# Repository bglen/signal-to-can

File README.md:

# signal-to-can device

Measures analog and digital signals and converts readings to CAN bus messages. Easilly powered by 12V automotive systems to make CAN bus datalogging in your vehicle easy.

- 8 ADC inputs with seperate signal grounds
  
- CAN 2.0b communication output
  
- Fully configurable through the CAN interface
  
- 3.3V and 5V sensor power supply
  
- Easilly powered by 12V automotive systems

- Per-channel configurable voltage offset and scaling

- Per-channel configurable out-of-range limits

- Pre-made DBC file you can use or edit as a template

### Enclosure

The repo contains a 3D-printable enclosure. We reccomend ASA, ABS, PC-ABS, or Nylon for automotive enviornments.

Front            |  Rear
:-------------------------:|:-------------------------:
  |  

### TODO
- Update board with schematic changes
- Calibration test points
- Choose new potentiometer for rev 2
- configuration CAN message

# CAN Messages

All messages are big-endian (Motorola).

## Output Messages

| Name             | ID            | DLC     | Bytes 0-1 | Bytes 2-3 | Bytes 4-5 | Bytes 6-7 |
| -----------      | -----------   | ------- | --------- | --------- | --------- | --------- |
| ADC Values 0 - 3 | node_id + 0x1 | 8 bytes | adc_0     | adc_1     | adc_2     | adc_3     |
| ADC Values 4 - 7 | node_id + 0x2 | 8 bytes | adc_4     | adc_5     | adc_6     | adc_7     |

| Name          | ID            | DLC     | Bytes 0-1  | Bytes 2-3 | Bytes 4-5 | Bytes 6-7  |
| -----------   | -----------   | ------- | ---------- | --------- | --------- | ---------- |
| Device Status | node_id + 0x3 | 8 bytes | adc_status | uptime    | v_supply  | fw_version |

### Parameters

**adc_0 to adc_7:** uint16, ontains the output value for each analog channel.

**adc_status:** uint16, Bit structure containing the current status for each channel. Each channel gets two bits starting with channel 0 to channel 7.

| 2-bit value  | Status            |
| -----------  | ----------------- |
| 00           | Inactive          |
| 01           | Active            |
| 10           | Out-of-range low  |
| 11           | Out-of-range high |

Example: adc_satus = 00011001010111 -> channel 0 inactive, channel 1 active, channel 3 out-of-range low, channel 4 active, channel 5 active, channel 6 active, channel 7 out-of-range high.

**uptime:** uint16, Seconds since power-on, wraps at 65535.

**v_supply:** uint16, Device supply voltage in mV.

**fw_version** uint16, Device firmware version.

## Command Message

A single CAN ID is used for all command messages. The device will respond with an acknoledge message after receiving the command message.

| Name            | ID            | DLC     | Byte 0  | Byte 1 | Byte 2 | Byte 3 | Byte 4 | Byte 5 | Byte 6 | Byte 7 |
| -----------     | ------------- | ------- | ------- | -----  | -----  | -----  | -----  | -----  | -----  | -----  |
| Command Message | node_id + 0x5 | 8 bytes | com     | d1     | d2     | d3     | d4     | d5     | d6     | d7     |
| Ack Message     | node_id + 0x6 | 1 bytes | success |        |        |        |        |        |        |        |

### Command Codes

| Command Name       | Command Code (com) | d1             | d2             | d3              | d4              | d5         | d6        | d7 |
| ------------------ | ------------------ | -------------- | -------------- | --------------- | --------------- | ---------- | --------- | -- |
| SET_BAUD           | 1                  | baud_enum      | 0              | 0               | 0               | 0          | 0         | 0  |
| SET_SAMPLE_RATE    | 2                  | sample_rate[0] | sample_rate[1] | 0               | 0               | 0          | 0         | 0  |
| SET_CHANNEL        | 3                  | channel        | enable_bit     | scale_factor[0] | scale_factor[1] | offset[0]  | offset[1] | 0  |
| SET_CHANNEL_RANGE  | 4                  | channel        | oor_min[0]     | oor_min[1]      | oor_max[0]      | oor_max[1] | 0         | 0  |
| GET_VALUE          | 5                  | channel        | selection      | 0               | 0               | 0          | 0         | 0  |

### Parameters

**com:** uint8, Command code. Use the table below to specify a particular command and structure the data

**d1 to d5 :** unint8, Command-specific data.

**success:** uint8, 1 if command executed successfully, 0 if there was an error.

**baud_enum:** uint8, Enum representing the desired baud rate.

| baud_enum | Baud Rate |
| --------- | --------- |
| 0         | 125 kbps  |
| 1         | 250 kbps  |
| 2         | 500 kbps  |
| 3         | 1 Mbps    |

**sample_rate:** uint16, Sample rate of the device in Hz. All channels are sampled at the same rate.

**channel:** uint8, Channel number from 0 to 7.

**enable_bit:** uint8, 0 -> inactive, 1 -> active.

**scale_factor:** uint16, Scale factor to convert the channel voltage to a useful value.

**offset:** uint16, Channel offset value, used with scale factor to convert the channel voltage to a useful value.

**oor_min:** uint16, Out of range minimum value. Used to detect issues with the channel, wiring, or sensor. Specify as a voltage in milivolts, from 0 to 3300. Must be less than the oor_max for that channel.

**oor_max:** uint16, Out of range maximum value. Used to detect issues with the channel, wiring, or sensor. Specify as a voltage in milivolts, from 0 to 3300.

**selection:** uint8, Enum representing the desired value to be returned.

| selection | Value to be returned |
| --------- | -------------------- |
| 0         | sample_rate          |
| 1         | scale_factor         |
| 2         | offset               |
| 3         | oor_min              |
| 4         | oor_max              |

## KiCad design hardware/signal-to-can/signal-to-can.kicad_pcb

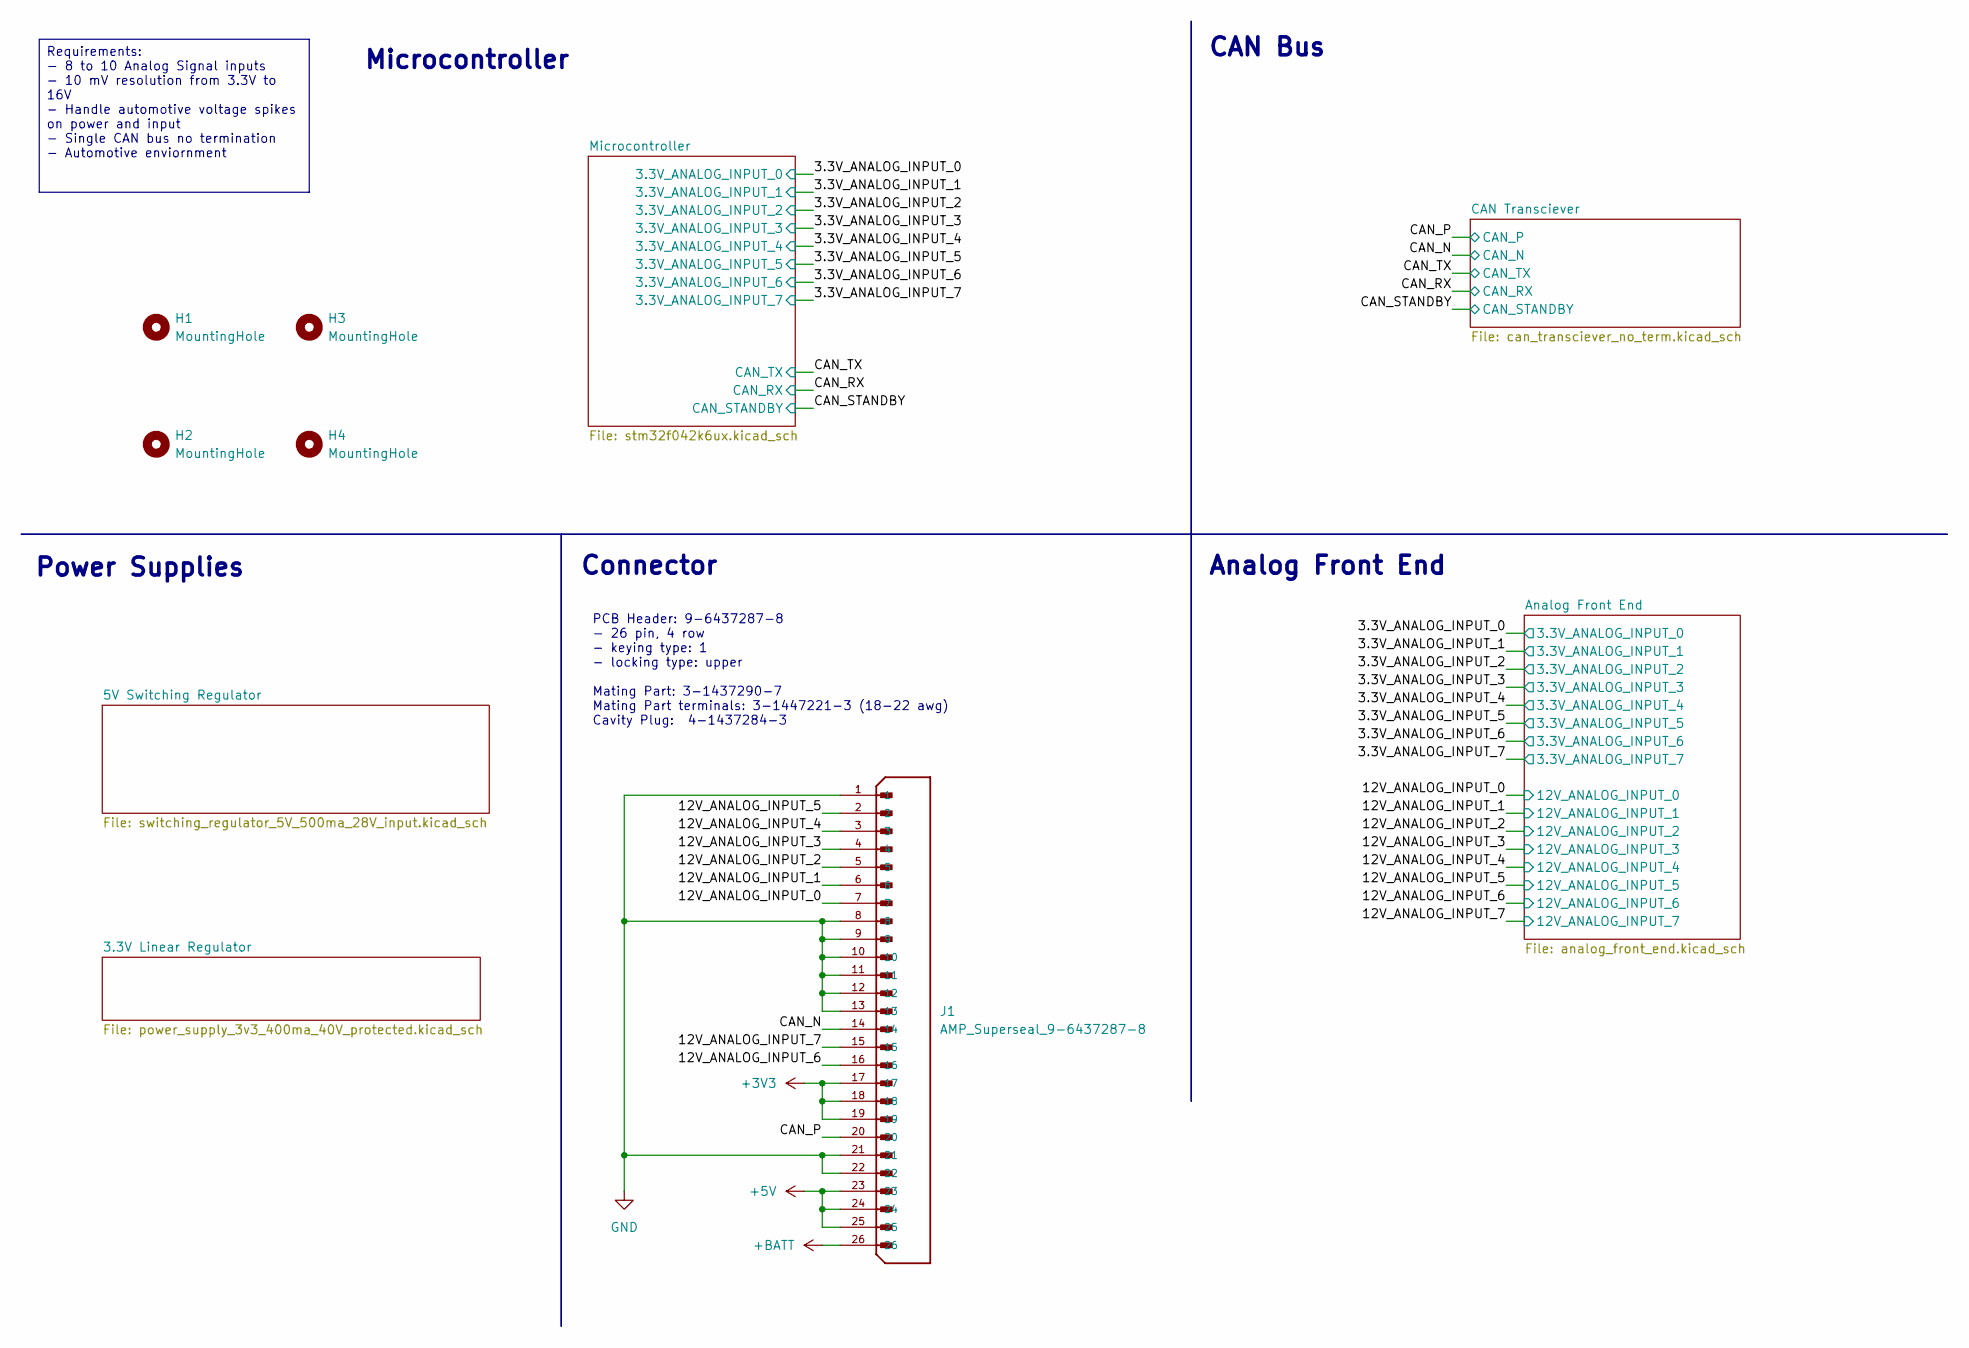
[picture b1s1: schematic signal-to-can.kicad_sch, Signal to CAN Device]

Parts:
H1, H2, H3, H4: MountingHole; MountingHole_3.2mm_M3
J1: AMP_Superseal_9-6437287-8; TE_9-6437287-8_1; PARTREV A1

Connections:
+3V3: J1.17, J1.18, J1.19; also elsewhere on the board
+5V: J1.23, J1.24, J1.25; also elsewhere on the board
+BATT: J1.26; also elsewhere on the board
/12V_ANALOG_INPUT_0: J1.7; also elsewhere on the board
/12V_ANALOG_INPUT_1: J1.6; also elsewhere on the board
/12V_ANALOG_INPUT_2: J1.5; also elsewhere on the board
/12V_ANALOG_INPUT_3: J1.4; also elsewhere on the board
/12V_ANALOG_INPUT_4: J1.3; also elsewhere on the board
/12V_ANALOG_INPUT_5: J1.2; also elsewhere on the board
/12V_ANALOG_INPUT_6: J1.16; also elsewhere on the board
/12V_ANALOG_INPUT_7: J1.15; also elsewhere on the board
/CAN_N: J1.14; also elsewhere on the board
/CAN_P: J1.20; also elsewhere on the board
GND: J1.1, J1.8, J1.9, J1.10, J1.11, J1.12, J1.13, J1.21, J1.22; also elsewhere on the board

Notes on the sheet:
Connector
Analog Front End
PCB Header: 9-6437287-8 - 26 pin, 4 row - keying type: 1 - locking type: upper Mating Part: 3-1437290-7 Mating Part terminals: 3-1447221-3 (18-22 awg) Cavity Plug: 4-1437284-3
Power Supplies
CAN Bus
Microcontroller
Requirements: - 8 to 10 Analog Signal inputs - 10 mV resolution from 3.3V to 16V - Handle automotive voltage spikes on power and input - Single CAN bus no termination - Automotive enviornment

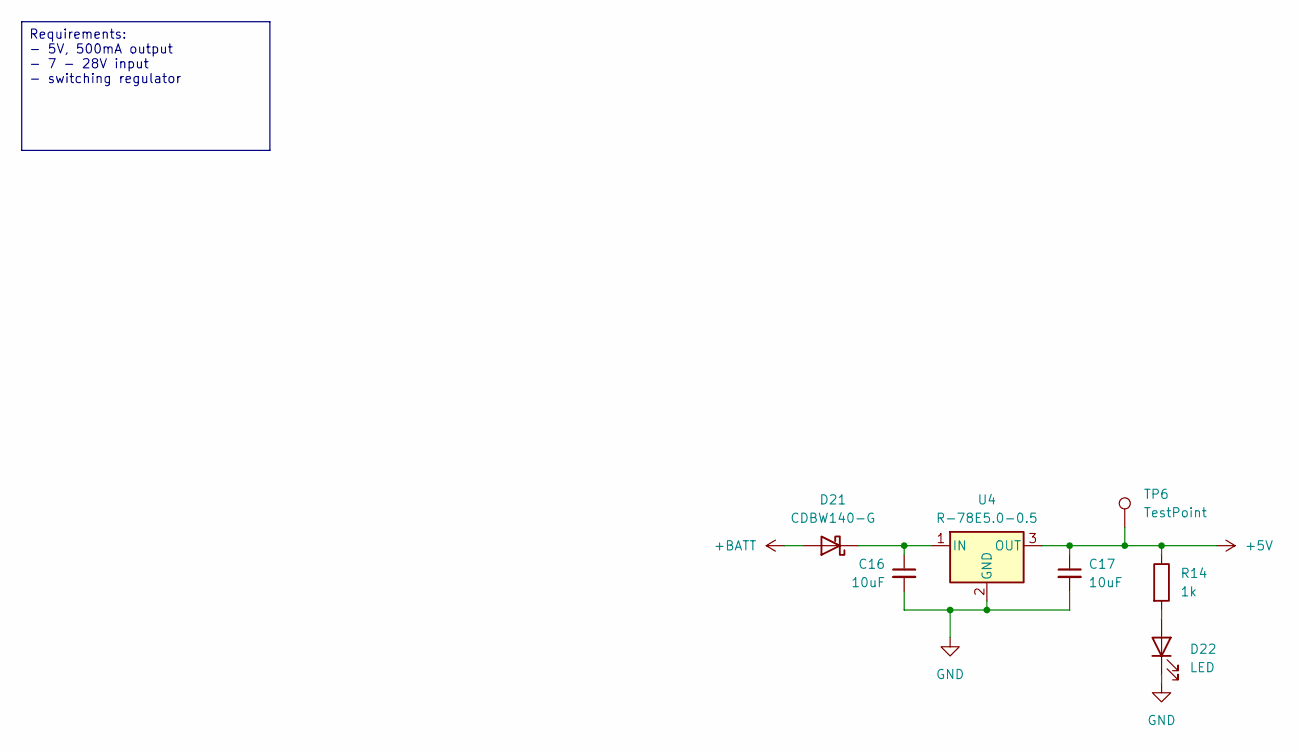
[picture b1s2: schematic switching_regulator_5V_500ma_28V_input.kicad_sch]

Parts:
C16, C17: 10uF; C_0603_1608Metric
D21: CDBW140-G; D_SOD-123
D22: LED; LED_0603_1608Metric
R14: 1k; R_0603_1608Metric
TP6: TestPoint; TestPoint_Pad_D1.0mm
U4: R-78E5.0-0.5; Converter_DCDC_RECOM_R-78E-0.5_THT

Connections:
+5V: C17.1, R14.1, TP6.1, U4.3 (OUT); also elsewhere on the board
+BATT: D21.2 (A); also elsewhere on the board
GND: C16.2, C17.2, D22.1 (K), U4.2 (GND); also elsewhere on the board
unnamed: C16.1, D21.1 (K), U4.1 (IN)
unnamed: D22.2 (A), R14.2

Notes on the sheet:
Requirements: - 5V, 500mA output - 7 - 28V input - switching regulator

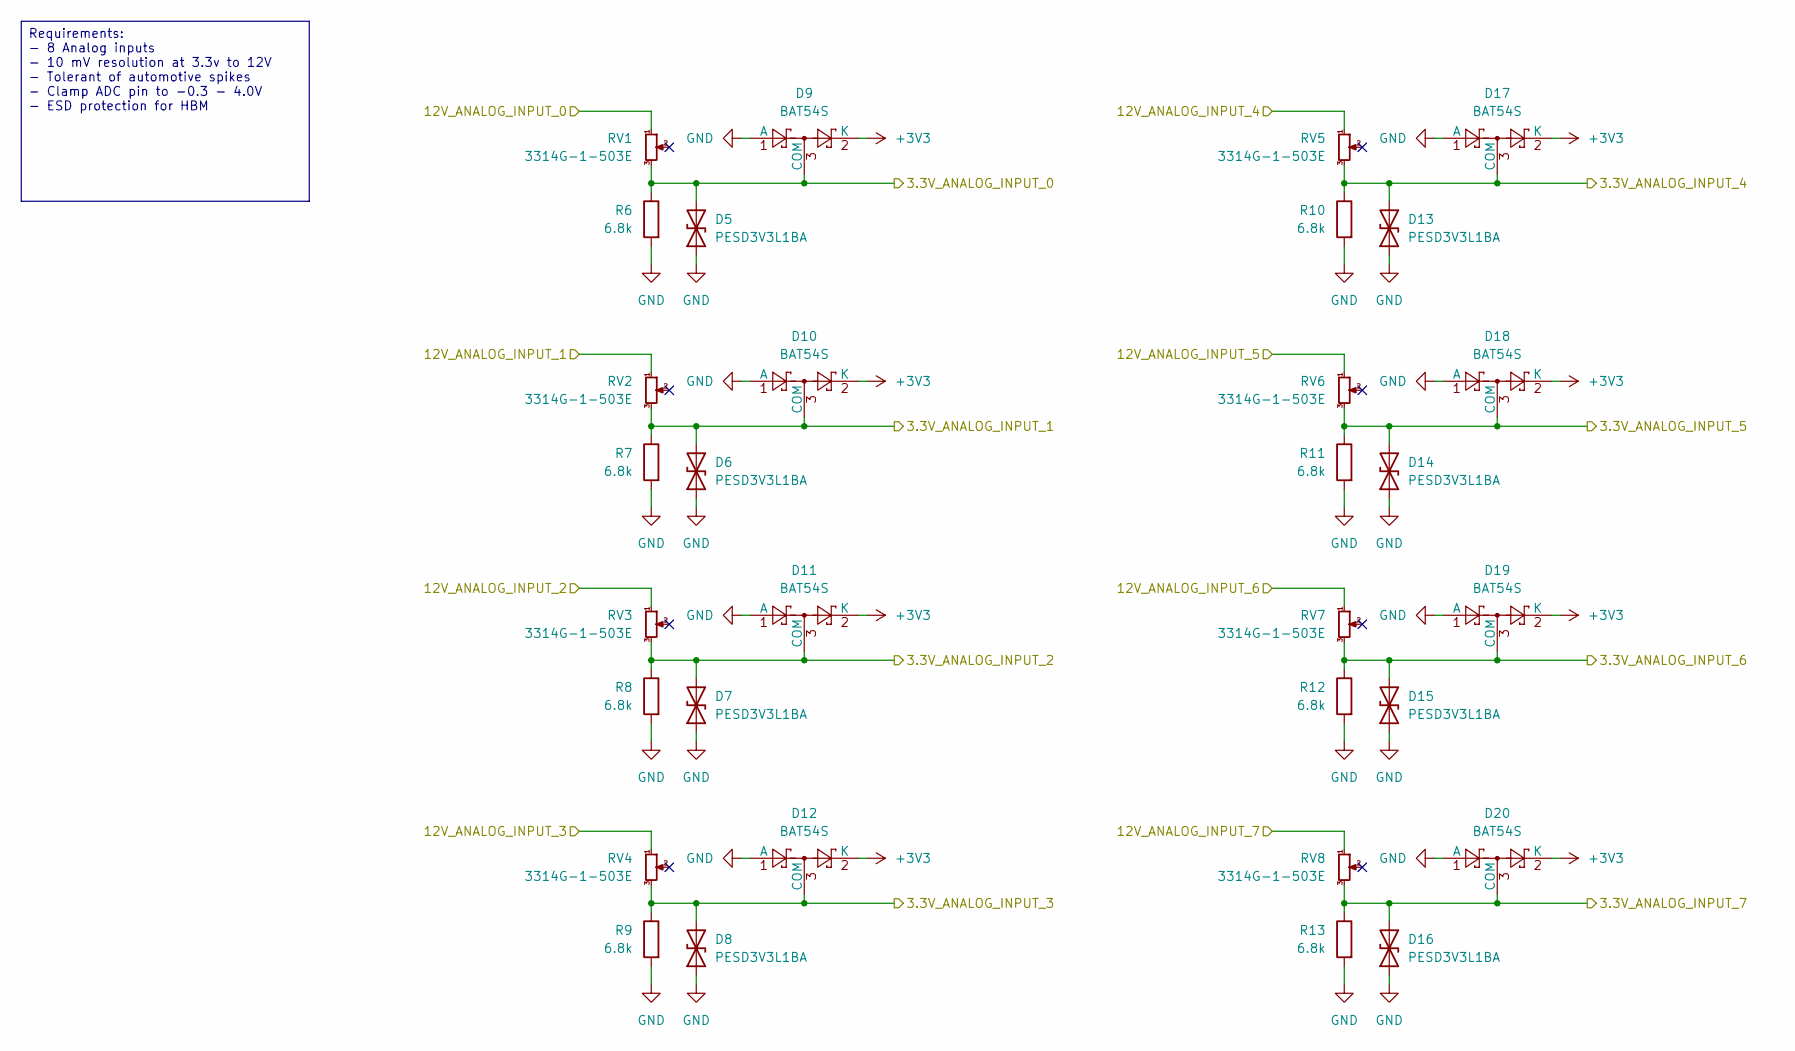
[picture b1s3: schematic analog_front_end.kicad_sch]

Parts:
D5, D6, D7, D8, D13, D14, D15, D16: PESD3V3L1BA; D_SOD-323
D9, D10, D11, D12, D17, D18, D19, D20: BAT54S; SOT-23
R6, R7, R8, R9, R10, R11, R12, R13: 6.8k; R_0603_1608Metric
RV1, RV2, RV3, RV4, RV5, RV6, RV7, RV8: 3314G-1-503E; Potentiometer_Bourns_3314G_Vertical

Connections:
+3V3: D9.2 (K), D10.2 (K), D11.2 (K), D12.2 (K), D17.2 (K), D18.2 (K), D19.2 (K), D20.2 (K); also elsewhere on the board
/3.3V_ANALOG_INPUT_0: D5.2 (A2), D9.3 (COM), R6.1, RV1.3; also elsewhere on the board
/3.3V_ANALOG_INPUT_1: D6.2 (A2), D10.3 (COM), R7.1, RV2.3; also elsewhere on the board
/3.3V_ANALOG_INPUT_2: D7.2 (A2), D11.3 (COM), R8.1, RV3.3; also elsewhere on the board
/3.3V_ANALOG_INPUT_3: D8.2 (A2), D12.3 (COM), R9.1, RV4.3; also elsewhere on the board
/3.3V_ANALOG_INPUT_4: D13.2 (A2), D17.3 (COM), R10.1, RV5.3; also elsewhere on the board
/3.3V_ANALOG_INPUT_5: D14.2 (A2), D18.3 (COM), R11.1, RV6.3; also elsewhere on the board
/3.3V_ANALOG_INPUT_6: D15.2 (A2), D19.3 (COM), R12.1, RV7.3; also elsewhere on the board
/3.3V_ANALOG_INPUT_7: D16.2 (A2), D20.3 (COM), R13.1, RV8.3; also elsewhere on the board
/12V_ANALOG_INPUT_0: RV1.1; also elsewhere on the board
/12V_ANALOG_INPUT_1: RV2.1; also elsewhere on the board
/12V_ANALOG_INPUT_2: RV3.1; also elsewhere on the board
/12V_ANALOG_INPUT_3: RV4.1; also elsewhere on the board
/12V_ANALOG_INPUT_4: RV5.1; also elsewhere on the board
/12V_ANALOG_INPUT_5: RV6.1; also elsewhere on the board
/12V_ANALOG_INPUT_6: RV7.1; also elsewhere on the board
/12V_ANALOG_INPUT_7: RV8.1; also elsewhere on the board
GND: D5.1 (A1), D6.1 (A1), D7.1 (A1), D8.1 (A1), D9.1 (A), D10.1 (A), D11.1 (A), D12.1 (A), D13.1 (A1), D14.1 (A1), D15.1 (A1), D16.1 (A1), D17.1 (A), D18.1 (A), D19.1 (A), D20.1 (A), R6.2, R7.2, R8.2, R9.2, R10.2, R11.2, R12.2, R13.2; also elsewhere on the board

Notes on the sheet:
Requirements: - 8 Analog inputs - 10 mV resolution at 3.3v to 12V - Tolerant of automotive spikes - Clamp ADC pin to -0.3 - 4.0V - ESD protection for HBM

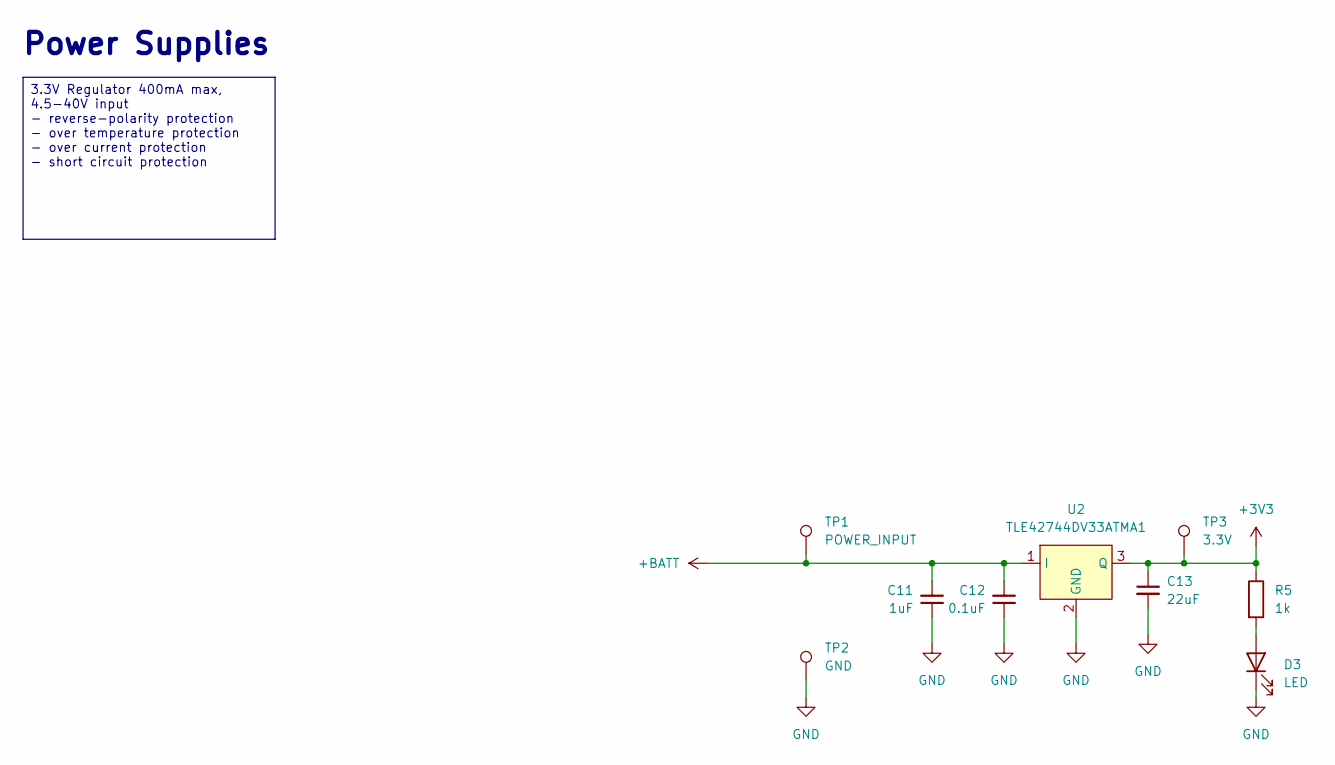
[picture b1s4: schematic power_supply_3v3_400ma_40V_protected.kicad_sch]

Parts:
C11: 1uF; C_0603_1608Metric
C12: 0.1uF; C_0603_1608Metric
C13: 22uF; C_0805_2012Metric
D3: LED; LED_0603_1608Metric
R5: 1k; R_0603_1608Metric
TP1: POWER_INPUT; TestPoint_Pad_D1.0mm
TP2: GND; TestPoint_Pad_D1.0mm
TP3: 3.3V; TestPoint_Pad_D1.0mm
U2: TLE42744DV33ATMA1; TO-252-3_TabPin2

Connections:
+3V3: C13.1, R5.1, TP3.1, U2.3 (Q); also elsewhere on the board
+BATT: C11.2, C12.2, TP1.1, U2.1 (I); also elsewhere on the board
GND: C11.1, C12.1, C13.2, D3.1 (K), TP2.1, U2.2 (GND); also elsewhere on the board
unnamed: D3.2 (A), R5.2

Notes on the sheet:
Power Supplies
3.3V Regulator 400mA max, 4.5-40V input - reverse-polarity protection - over temperature protection - over current protection - short circuit protection

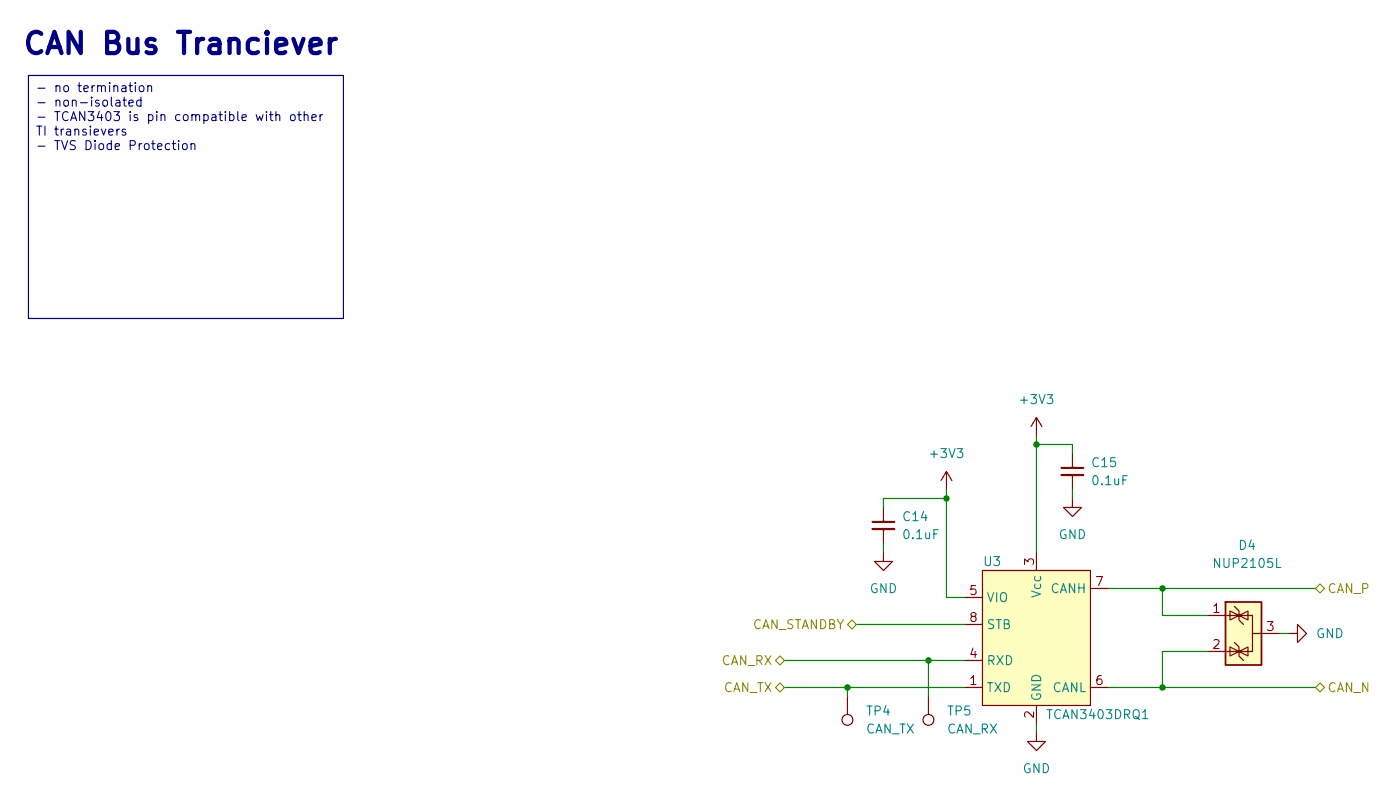
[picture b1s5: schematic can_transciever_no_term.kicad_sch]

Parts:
C14, C15: 0.1uF; C_0603_1608Metric
D4: NUP2105L; SOT-23
TP4: CAN_TX; TestPoint_Pad_D1.0mm
TP5: CAN_RX; TestPoint_Pad_D1.0mm
U3: TCAN3403DRQ1; SOIC-8_3.9x4.9mm_P1.27mm

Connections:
+3V3: C14.1, C15.1, U3.3 (Vcc), U3.5 (VIO); also elsewhere on the board
/CAN_N: D4.2 (K), U3.6 (CANL); also elsewhere on the board
/CAN_P: D4.1 (K), U3.7 (CANH); also elsewhere on the board
/CAN_RX: TP5.1, U3.4 (RXD); also elsewhere on the board
/CAN_STANDBY: U3.8 (STB); also elsewhere on the board
/CAN_TX: TP4.1, U3.1 (TXD); also elsewhere on the board
GND: C14.2, C15.2, D4.3 (A), U3.2 (GND); also elsewhere on the board

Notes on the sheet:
CAN Bus Tranciever
- no termination - non-isolated - TCAN3403 is pin compatible with other TI transievers - TVS Diode Protection

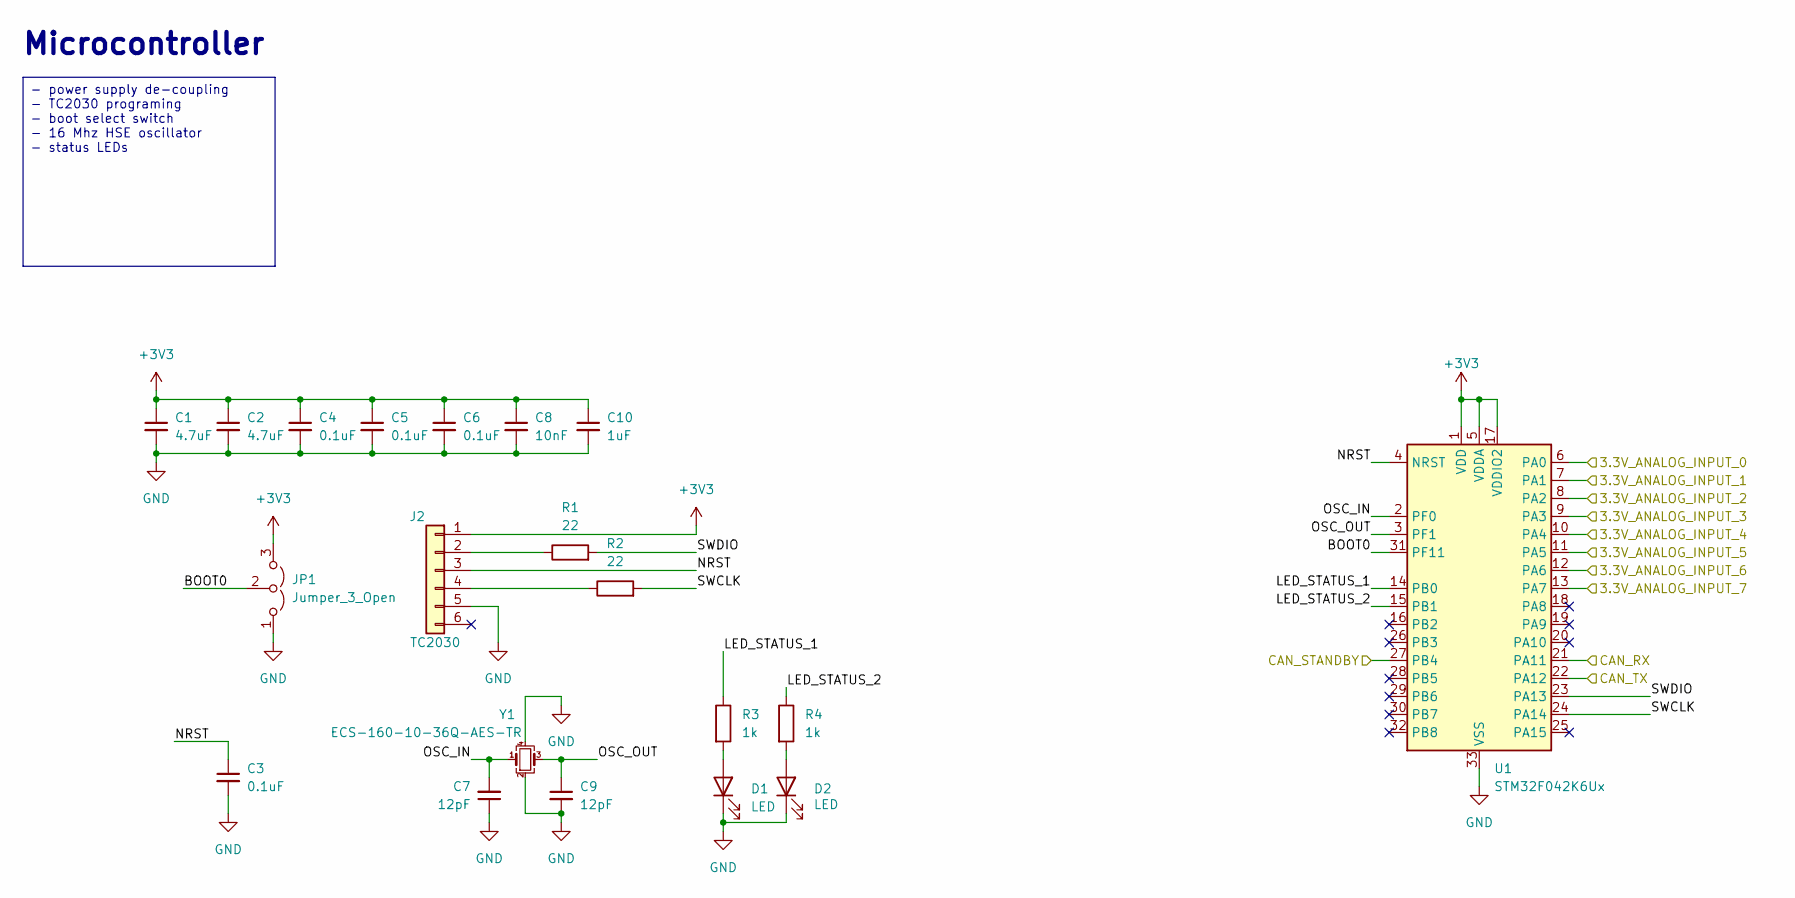
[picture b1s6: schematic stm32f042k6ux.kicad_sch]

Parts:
C1, C2: 4.7uF; C_0603_1608Metric
C3, C4, C5, C6: 0.1uF; C_0603_1608Metric
C7, C9: 12pF; C_0603_1608Metric
C8: 10nF; C_0603_1608Metric
C10: 1uF; C_0603_1608Metric
D1, D2: LED; LED_0603_1608Metric
J2: TC2030; Tag-Connect_TC2030-IDC-NL_2x03_P1.27mm_Vertical
JP1: Jumper_3_Open; SolderJumper-3_P1.3mm_Open_RoundedPad1.0x1.5mm
R1, R2: 22; R_0603_1608Metric
R3, R4: 1k; R_0603_1608Metric
U1: STM32F042K6Ux; QFN-32-1EP_5x5mm_P0.5mm_EP3.45x3.45mm
Y1: ECS-160-10-36Q-AES-TR; Crystal_SMD_2520-4Pin_2.5x2.0mm

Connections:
+3V3: C1.1, C2.1, C4.1, C5.1, C6.1, C8.1, C10.1, J2.1, JP1.3 (B), U1.1 (VDD), U1.5 (VDDA), U1.17 (VDDIO2); also elsewhere on the board
/3.3V_ANALOG_INPUT_0: U1.6 (PA0); also elsewhere on the board
/3.3V_ANALOG_INPUT_1: U1.7 (PA1); also elsewhere on the board
/3.3V_ANALOG_INPUT_2: U1.8 (PA2); also elsewhere on the board
/3.3V_ANALOG_INPUT_3: U1.9 (PA3); also elsewhere on the board
/3.3V_ANALOG_INPUT_4: U1.10 (PA4); also elsewhere on the board
/3.3V_ANALOG_INPUT_5: U1.11 (PA5); also elsewhere on the board
/3.3V_ANALOG_INPUT_6: U1.12 (PA6); also elsewhere on the board
/3.3V_ANALOG_INPUT_7: U1.13 (PA7); also elsewhere on the board
/CAN_RX: U1.21 (PA11); also elsewhere on the board
/CAN_STANDBY: U1.27 (PB4); also elsewhere on the board
/CAN_TX: U1.22 (PA12); also elsewhere on the board
/Microcontroller/BOOT0: JP1.2 (C), U1.31 (PF11)
/Microcontroller/LED_STATUS_1: R3.1, U1.14 (PB0)
/Microcontroller/LED_STATUS_2: R4.1, U1.15 (PB1)
/Microcontroller/NRST: C3.1, J2.3, U1.4 (NRST)
/Microcontroller/OSC_IN: C7.2, U1.2 (PF0), Y1.1
/Microcontroller/OSC_OUT: C9.1, U1.3 (PF1), Y1.3
/Microcontroller/SWCLK: R2.2, U1.24 (PA14)
/Microcontroller/SWDIO: R1.2, U1.23 (PA13)
GND: C1.2, C2.2, C3.2, C4.2, C5.2, C6.2, C7.1, C8.2, C9.2, C10.2, D1.1 (K), D2.1 (K), J2.5, JP1.1 (A), U1.33 (VSS), Y1.2, Y1.4; also elsewhere on the board
unnamed: D1.2 (A), R3.2
unnamed: D2.2 (A), R4.2
unnamed: J2.2, R1.1
unnamed: J2.4, R2.1

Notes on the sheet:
Microcontroller
- power supply de-coupling - TC2030 programing - boot select switch - 16 Mhz HSE oscillator - status LEDs

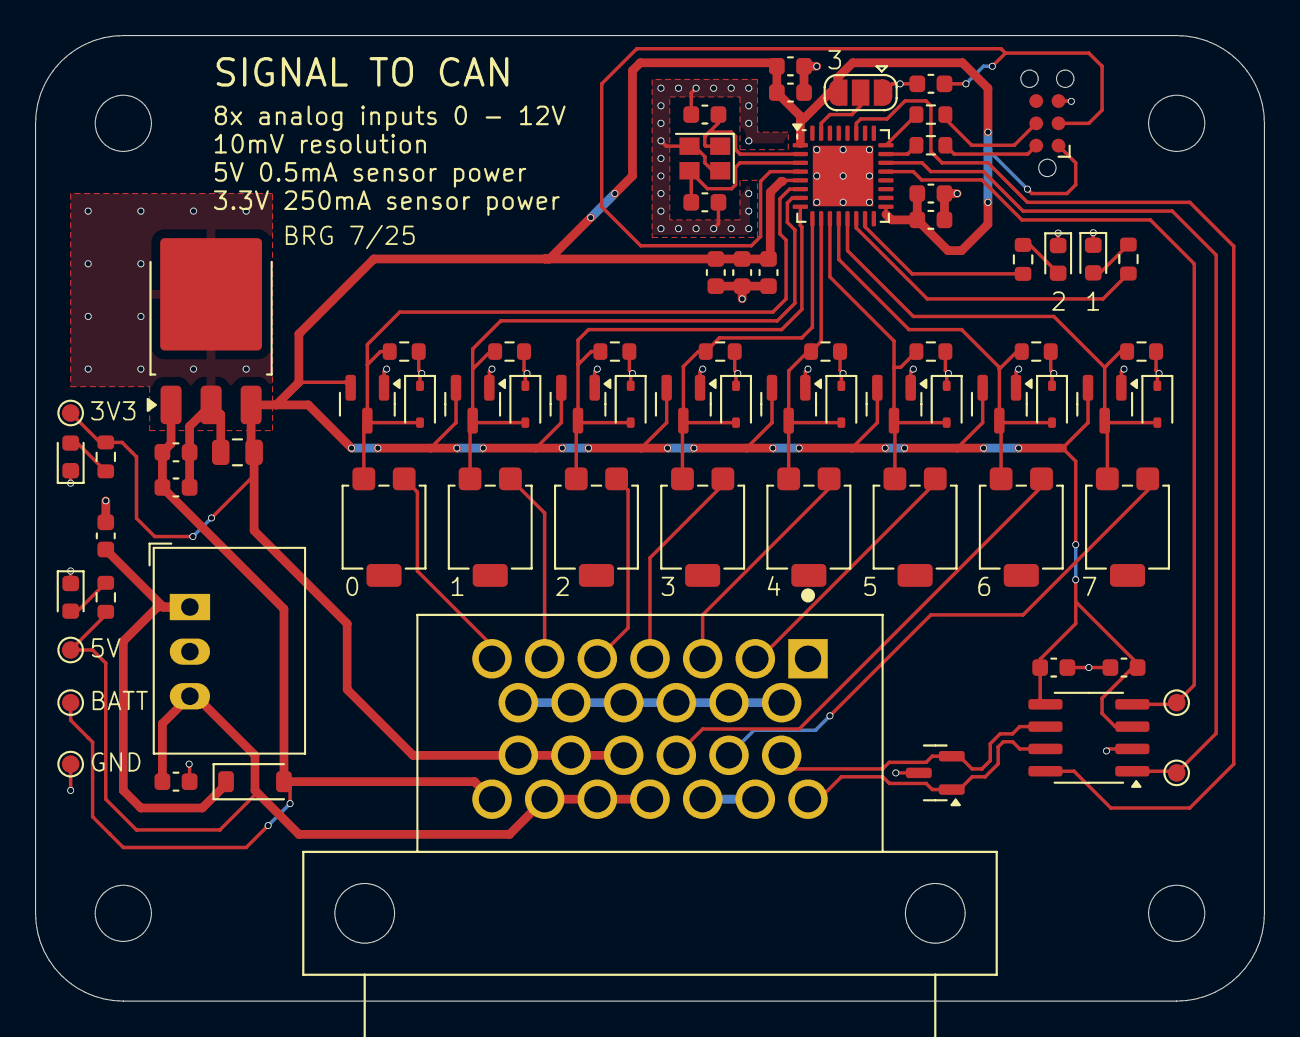
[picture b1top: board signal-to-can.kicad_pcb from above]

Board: 2 copper layers, 70.0 x 55.0 mm, 79 parts (0 on the bottom side), 40 nets.

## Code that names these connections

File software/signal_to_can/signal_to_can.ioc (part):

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Mcu.Name=STM32F042K(4-6)Tx
Mcu.Package=LQFP32
Mcu.UserName=STM32F042K6Tx
PA0.Mode=IN0
PA0.Signal=ADC_IN0
PA1.Mode=IN1
PA1.Signal=ADC_IN1
PA11.GPIOParameters=GPIO_Speed,GPIO_PuPd
PA11.GPIO_PuPd=GPIO_PULLUP
PA11.GPIO_Speed=GPIO_SPEED_FREQ_HIGH
PA11.Mode=CAN_Activate
PA11.Signal=CAN_RX
PA12.GPIOParameters=GPIO_PuPd
PA12.GPIO_PuPd=GPIO_NOPULL
PA12.Mode=CAN_Activate
PA12.Signal=CAN_TX
PA13.Mode=Serial_Wire
PA13.Signal=SYS_SWDIO
PA14.Mode=Serial_Wire
PA14.Signal=SYS_SWCLK
PA2.Mode=IN2
PA2.Signal=ADC_IN2
PA3.Mode=IN3
PA3.Signal=ADC_IN3
PA4.Mode=IN4
PA4.Signal=ADC_IN4
PA5.Mode=IN5
PA5.Signal=ADC_IN5
PA6.Mode=IN6
PA6.Signal=ADC_IN6
PA7.Mode=IN7
PA7.Signal=ADC_IN7
PB0.GPIOParameters=GPIO_Label
PB0.GPIO_Label=LED_STATUS_1
PB0.Signal=GPIO_Output
PB1.GPIOParameters=GPIO_Label
PB1.GPIO_Label=LED_STATUS_2
PB1.Signal=GPIO_Output
PB4.GPIOParameters=GPIO_Label
PB4.GPIO_Label=CAN_STANDBY
PB4.Signal=GPIO_Output
PF0-OSC_IN.Mode=HSE-External-Oscillator
PF0-OSC_IN.Signal=RCC_OSC_IN
PF1-OSC_OUT.Mode=HSE-External-Oscillator
PF1-OSC_OUT.Signal=RCC_OSC_OUT
RCC.HSE_VALUE=16000000
RCC.SYSCLKFreq_VALUE=48000000
RCC.SYSCLKSource=RCC_SYSCLKSOURCE_PLLCLK
board=custom

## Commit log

2025-07-21 AFE, power supply, connector
    Ready for PCB layout
2025-07-22 1st rev PCB layout
2025-07-22 production v1
2025-08-06 Initial firmware
    - poll ADCs and send converted messages at a given rate
    - config message to enable / disable inputs and adjust scaling factors.
2025-08-12 Working CAN peripheral
    - heartbeat
    - test can message
    - adc module compiling
2025-08-13 ADC configuration
    - updated README
    Todo:
    - fix potentiometer wiring in schematic
    - add divider test points
    - bigger ground test point
    - Fix tranceiver Vdd (should be 5V)
2025-08-13 enclosure
2025-08-13 Use DMA & Scan mode for ADC module
    - verified test works
2025-08-14 Updated CAD
    - easier to print on side for ASA
    - accounted for thru hole pins
    - fixed issue with lid and assembly around connector
2025-08-14 Message processing module
    business logic for device on top of peripheral drivers
2025-08-14 Updated documentation
2025-08-14 Added DBC file
